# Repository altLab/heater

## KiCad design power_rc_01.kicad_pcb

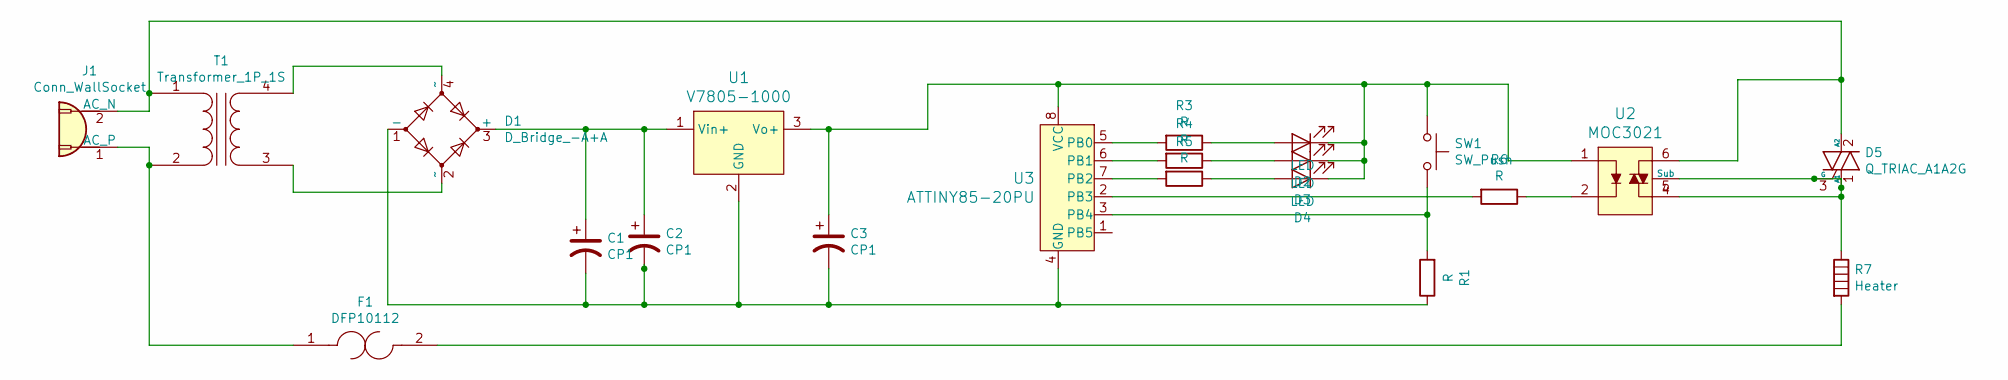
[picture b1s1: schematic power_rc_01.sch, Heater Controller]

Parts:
C1, C2, C3: CP1; CP_Radial_D5.0mm_P2.50mm
D1: D_Bridge_-A+A; Diode_Bridge_15.7x15.7x6.3mm_P10.8mm
D2, D3, D4: LED; LED_D3.0mm_Horizontal_O3.81mm_Z10.0mm
D5: Q_TRIAC_A1A2G; TO-218-3_Horizontal_TabUp
F1: DFP10112; Fuseholder_Cylinder-5x20mm_Schurter_0031_8201_Horizontal_Op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; MPN DFP10112; Digi-Key_PN 285-1901-ND
J1: Conn_WallSocket; SolderWirePad_1x02_P7.62mm_Drill2mm
R1, R3, R4, R5, R6: R; R_Axial_DIN0309_L9.0mm_D3.2mm_P2.54mm_Vertical
R7: Heater; JST_EH_B2B-EH-A_1x02_P2.50mm_Vertical
SW1: SW_Push; SW_PUSH_6mm
T1: Transformer_1P_1S; Transformer_37x44
U1: V7805-1000; 3-SIP_Module_V7805-1000; MPN V7805-1000; Digi-Key_PN 102-1715-ND
U2: MOC3021; DIP-6_W7.62mm; MPN MOC3021; Digi-Key_PN 160-1374-5-ND
U3: ATTINY85-20PU; DIP-8_W7.62mm; MPN ATTINY85-20PU; Digi-Key_PN ATTINY85-20PU-ND

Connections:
unnamed: C1.1, C2.1, D1.3 (+), U1.1 (Vin+)
unnamed: C1.2, C2.2, C3.2, D1.1 (-), R1.1, U1.2 (GND), U3.4 (GND)
unnamed: C3.1, D2.1 (K), D3.1 (K), D4.1 (K), SW1.1, U1.3 (Vo+), U2.1, U3.8 (VCC)
unnamed: D1.2 (~~), T1.3 (SA)
unnamed: D1.4 (~~), T1.4 (SB)
unnamed: D2.2 (A), R3.1
unnamed: D3.2 (A), R4.1
unnamed: D4.2 (A), R5.1
unnamed: D5.1 (A1), D5.3 (G), R7.1, U2.4, U2.5 (Sub)
unnamed: D5.2 (A2), J1.2 (AC_N), T1.1 (AA), U2.6
unnamed: F1.1, J1.1 (AC_P), T1.2 (AB)
unnamed: F1.2, R7.2
unnamed: R1.2, SW1.2, U3.3 (PB4)
unnamed: R3.2, U3.5 (PB0)
unnamed: R4.2, U3.6 (PB1)
unnamed: R5.2, U3.7 (PB2)
unnamed: R6.1, U2.2
unnamed: R6.2, U3.2 (PB3)

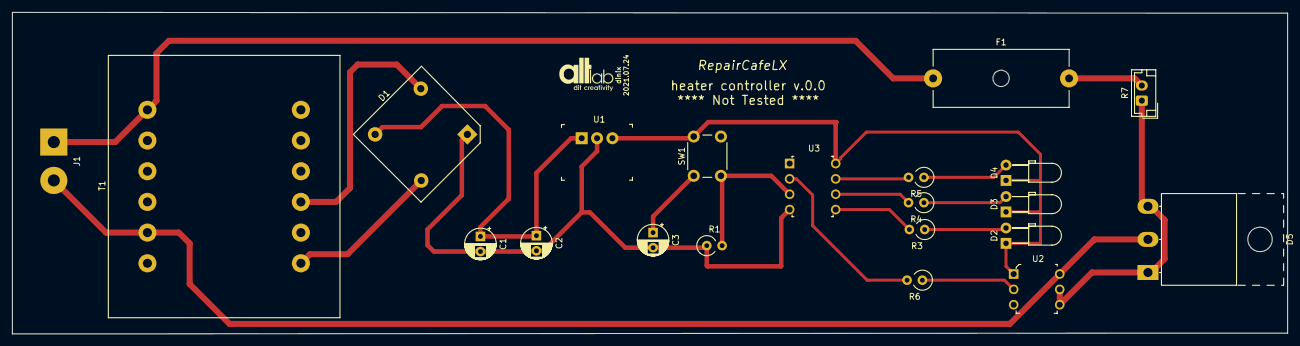
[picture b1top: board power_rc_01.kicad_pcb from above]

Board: 2 copper layers, 211.1 x 53.2 mm, 22 parts (0 on the bottom side), 18 nets.

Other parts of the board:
LOGO***: ALTLAB; ALTLAB_LOGO

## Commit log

2021-07-24 V0.0
